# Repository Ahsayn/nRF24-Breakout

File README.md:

# nRF24-Breakout
A nRF24 module breakout to easily interface it with breadboards. Done in KiCad 5.1.9

# About this Project
It's a simple breakout board for connecting nRF24 modules to a breadboard when prototyping. Source files provide the schematics and the custom footprint created. To use, clone the project and open it in KiCad. Check to ensure that the custom component and footprints are present before proceeding. Designed this while learning about PCB design in KiCad via the KiCad like a Pro course by Tech Explorations.

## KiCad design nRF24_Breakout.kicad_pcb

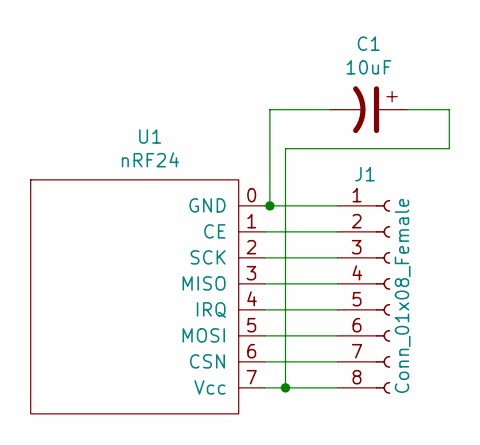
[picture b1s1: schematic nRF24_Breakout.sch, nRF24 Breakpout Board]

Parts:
C1: 10uF; CP_Radial_D10.0mm_P5.00mm
J1: Conn_01x08_Female; PinHeader_1x08_P2.54mm_Vertical
U1: nRF24

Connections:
unnamed: C1.1, J1.8, U1.7 (Vcc)
unnamed: C1.2, J1.1, U1.0 (GND)
unnamed: J1.2, U1.1 (CE)
unnamed: J1.3, U1.2 (SCK)
unnamed: J1.4, U1.3 (MISO)
unnamed: J1.5, U1.4 (IRQ)
unnamed: J1.6, U1.5 (MOSI)
unnamed: J1.7, U1.6 (CSN)

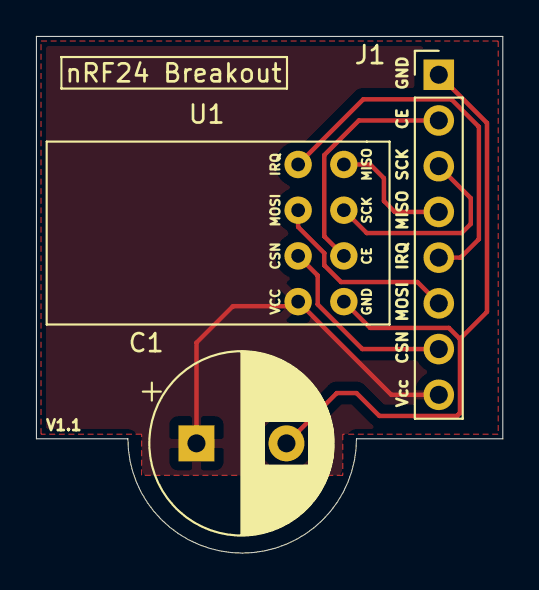
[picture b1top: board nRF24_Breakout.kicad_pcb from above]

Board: 2 copper layers, 25.9 x 28.7 mm, 3 parts (0 on the bottom side), 8 nets.

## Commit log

2021-10-23 Updated README with setup instructions
2021-10-23 Added schematic, custom component and footprint
2021-10-23 Added Initial PCB layout
2021-10-23 Updated Connector Pins
2021-10-23 Added tracks & labels
2021-10-24 Added filtering cap
2021-10-24 Added copper fill
2021-10-24 Generated Gerber Files
